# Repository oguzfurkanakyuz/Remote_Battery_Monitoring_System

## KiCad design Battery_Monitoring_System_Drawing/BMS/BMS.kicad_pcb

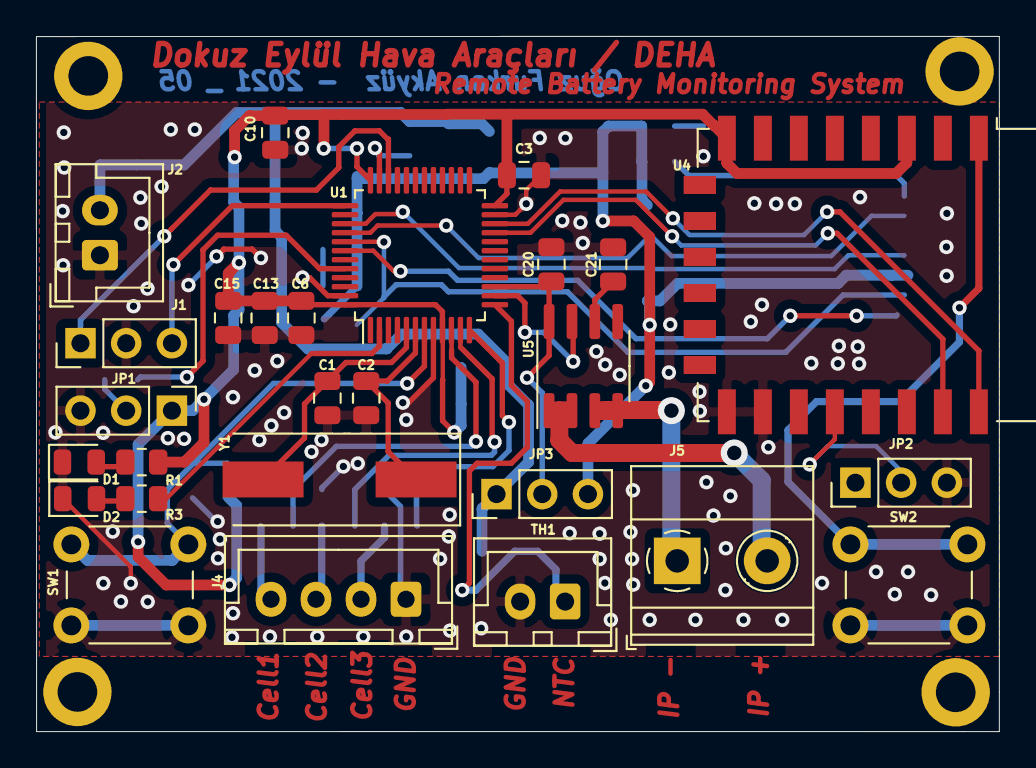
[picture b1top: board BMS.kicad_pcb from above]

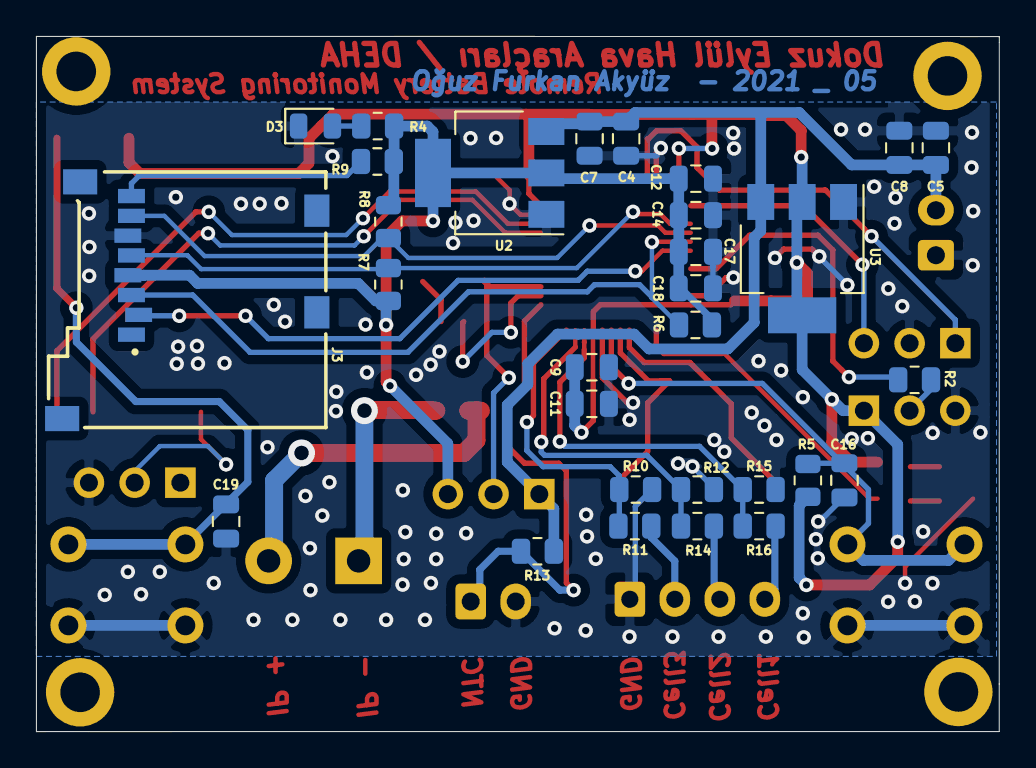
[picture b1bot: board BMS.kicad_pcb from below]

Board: 2 copper layers, 53.5 x 38.6 mm, 61 parts (30 on the bottom side), 36 nets.

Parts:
C1, C2: 22pF; C_0805_2012Metric
C3, C6, C7, C8, C9, C10, C14, C15, C16, C18, C19, C20: 100nF; C_0805_2012Metric
C4, C5, C12, C13, C17: 10uF; C_0805_2012Metric
C11: 1uF; C_0805_2012Metric
C21: 1nF; C_0805_2012Metric
D1, D2, D3: LED; LED_0805_2012Metric
H1, H2, H3, H4: Mounting_Hole; MountingHole_2.2mm_M2_DIN965_Pad
J1: SWD Pins; PinHeader_1x03_P2.54mm_Vertical
J2: INPUT 5V; JST_XH_B2B-XH-A_1x02_P2.50mm_Vertical
J3: 693071010811; micro_sd_8+1
J4: Conn_01x04; JST_XH_B4B-XH-A_1x04_P2.50mm_Vertical
J5: ACS INPUT; TerminalBlock_Phoenix_MKDS-1,5-2_1x02_P5.00mm_Horizontal
JP1: BOOT Jumper; PinHeader_1x03_P2.54mm_Vertical
JP2: ESP BOOT JUMPER; PinHeader_1x03_P2.54mm_Vertical
JP3: ACS SUPPLY; PinHeader_1x03_P2.54mm_Vertical
R1, R3, R4: 470; R_0805_2012Metric
R2, R5, R6, R7, R8, R9, R13: 10K; R_0805_2012Metric
R10, R12: 12K; R_0805_2012Metric
R11: 3.3K; R_0805_2012Metric
R14, R15: 22K; R_0805_2012Metric
R16: 68K; R_0805_2012Metric
SW1: SW_Push_Dual; SW_PUSH_6mm_H5mm
SW2: ESP RESET BUTTON; SW_PUSH_6mm_H5mm
TH1: NTC_10K; JST_XH_B2B-XH-A_1x02_P2.50mm_Vertical
U1: STM32F101C8Tx; LQFP-48_7x7mm_P0.5mm
U2, U3: AMS1117-3.3; SOT-223-3_TabPin2
U4: ESP-12E
U5: ACS712xLCTR-30A; SOIC-8_3.9x4.9mm_P1.27mm
Y1: 8M; Crystal_SMD_HC49-SD

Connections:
+3.3VA: C12.1, C14.1, C17.1, C18.1, J3.4, JP3.3, R4.2, R6.1, R7.1, R8.1, R9.1, U2.2
+3V3: C3.1, C6.1, C9.1, C10.1, C11.1, C13.1, C15.1, JP1.1, R1.2, R5.2, U1.9, U1.24, U1.36, U1.48, U3.2, U4.3, U4.8
+5V: C4.1, C5.1, C7.1, C8.1, J2.2, JP3.1, R13.1, U2.3, U3.3
/ESP_IO0: JP2.2, U4.18
/ESP_RST: C19.1, SW2.1, U4.1
/SD_CS: J3.2, U1.42
/SD_MISO: J3.7, R8.2, U1.40
/SD_MOSI: J3.3, R6.2, U1.41
/SD_SCLK: J3.5, R7.2, U1.39
ACS_OUT: U1.14, U5.7
ACS_SUPPLY: C20.2, JP3.2, U1.15, U5.8
BOOT0: R2.2, U1.44
CELL_1: R15.1, R16.2, U1.10
CELL_2: R12.1, R14.2, U1.11
CELL_3: R10.1, R11.2, U1.12
ESP_RX: U1.21, U4.21
ESP_TX: U1.22, U4.22
GND: C1.2, C2.2, C3.2, C4.2, C5.2, C6.2, C7.2, C8.2, C9.2, C10.2, C11.2, C12.2, C13.2, C14.2, C15.2, C16.2, C17.2, C18.2, C19.2, C20.1, C21.2, D1.1, D2.1, D3.1, J1.2, J2.1, J3.6, J4.1, JP1.3, JP2.3, R10.2, R12.2, R15.2, SW1.2, SW2.2, TH1.2, U1.8, U1.23, U1.35, U1.47, U2.1, U3.1, U4.15, U4.16, U5.5
NRST: C16.1, R5.1, SW1.1, U1.7
NTC: R13.2, TH1.1, U1.13
unnamed: C21.1, U5.6
unnamed: D1.2, R1.1
unnamed: D2.2, R3.1
unnamed: D3.2, R4.1
unnamed: J3.8, R9.2
unnamed: J4.2, R11.1
unnamed: J4.3, R14.1
unnamed: J4.4, R16.1
unnamed: J5.1, U5.3, U5.4
unnamed: J5.2, U5.1, U5.2
unnamed: JP1.2, R2.1
OSC_IN: C1.1, U1.5, Y1.2
OSC_OUT: C2.1, U1.6, Y1.1
SWCLK: J1.3, U1.37
SWDIO: J1.1, U1.34
TEST_PIN: R3.2, U1.2

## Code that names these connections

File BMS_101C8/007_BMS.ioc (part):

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PC15-OSC32_OUT.Mode=LSE-External-Oscillator
PD1-OSC_OUT.Mode=HSE-External-Oscillator
Mcu.UserName=STM32F101C8Tx
PB10.Mode=Asynchronous
PA3.GPIOParameters=GPIO_Label
PB6.GPIO_Label=SPI1_CS
PD0-OSC_IN.Signal=RCC_OSC_IN
PC14-OSC32_IN.Signal=RCC_OSC32_IN
PB11.Signal=USART3_RX
PA0-WKUP.Signal=ADCx_IN0
PD1-OSC_OUT.Signal=RCC_OSC_OUT
PA13.Signal=SYS_JTMS-SWDIO
PB11.Mode=Asynchronous
PB6.Signal=GPIO_Output
PC15-OSC32_OUT.Signal=RCC_OSC32_OUT
PA1.Signal=ADCx_IN1
PD0-OSC_IN.Mode=HSE-External-Oscillator
PB10.Signal=USART3_TX
PA5.Signal=ADCx_IN5
PB3.Mode=Full_Duplex_Master
board=custom
PB4.Mode=Full_Duplex_Master
PC14-OSC32_IN.Mode=LSE-External-Oscillator
PA14.Mode=Serial_Wire
PB5.Mode=Full_Duplex_Master
PA4.GPIOParameters=GPIO_Label
PA13.Mode=Serial_Wire
Mcu.Name=STM32F101C(8-B)Tx
PB6.GPIOParameters=GPIO_Label
PA2.Signal=ADCx_IN2
PB3.Signal=SPI1_SCK
PA4.Signal=ADCx_IN4
Mcu.Package=LQFP48
PB5.Signal=SPI1_MOSI
PA5.GPIO_Label=ACS_SUPPLY
PA14.Signal=SYS_JTCK-SWCLK
PA5.GPIOParameters=GPIO_Label
PA4.GPIO_Label=ACS_OUT
PB4.Signal=SPI1_MISO
PA3.GPIO_Label=NTC
PA3.Signal=ADCx_IN3

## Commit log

2021-03-27 Create stm32cubeide.project.prefs
    V1.0 Single module implementation
2021-03-27 V1.0 Single module implementation
2021-04-30 2021/04/30
    Tüm sistem yazılımı tamamlandı.
    KiCad çizimi eklendi.
2021-05-01 Şematik çizimi tamamlandı.
    Şematik çizimi ve footprint atamaları tamamlandı.
2021-05-02 Layout çizimi tamanlandı.
    Layout çizimi ilk şablonu tamamlandı.
2021-05-03 DRC hataları çözüldü.
    DRC hataları çözüldü ve SD Card 3D görüntüsü eklendi.
2021-05-03 Düzenleme yapıldı.
2021-05-04 Micro Sd kılıf eklendi.
    Sd kart holder kılıfı micro sd kart soket kılıfı ile değiştirildi.
2021-05-04 Layout_v2 çizimi tamamlandı.
2021-05-04 Layout'da düzenlemeler yapıldı.
2021-05-06 Çizim tamamlandı.
    DRC yapıldı ve hatalar düzeltildi.
